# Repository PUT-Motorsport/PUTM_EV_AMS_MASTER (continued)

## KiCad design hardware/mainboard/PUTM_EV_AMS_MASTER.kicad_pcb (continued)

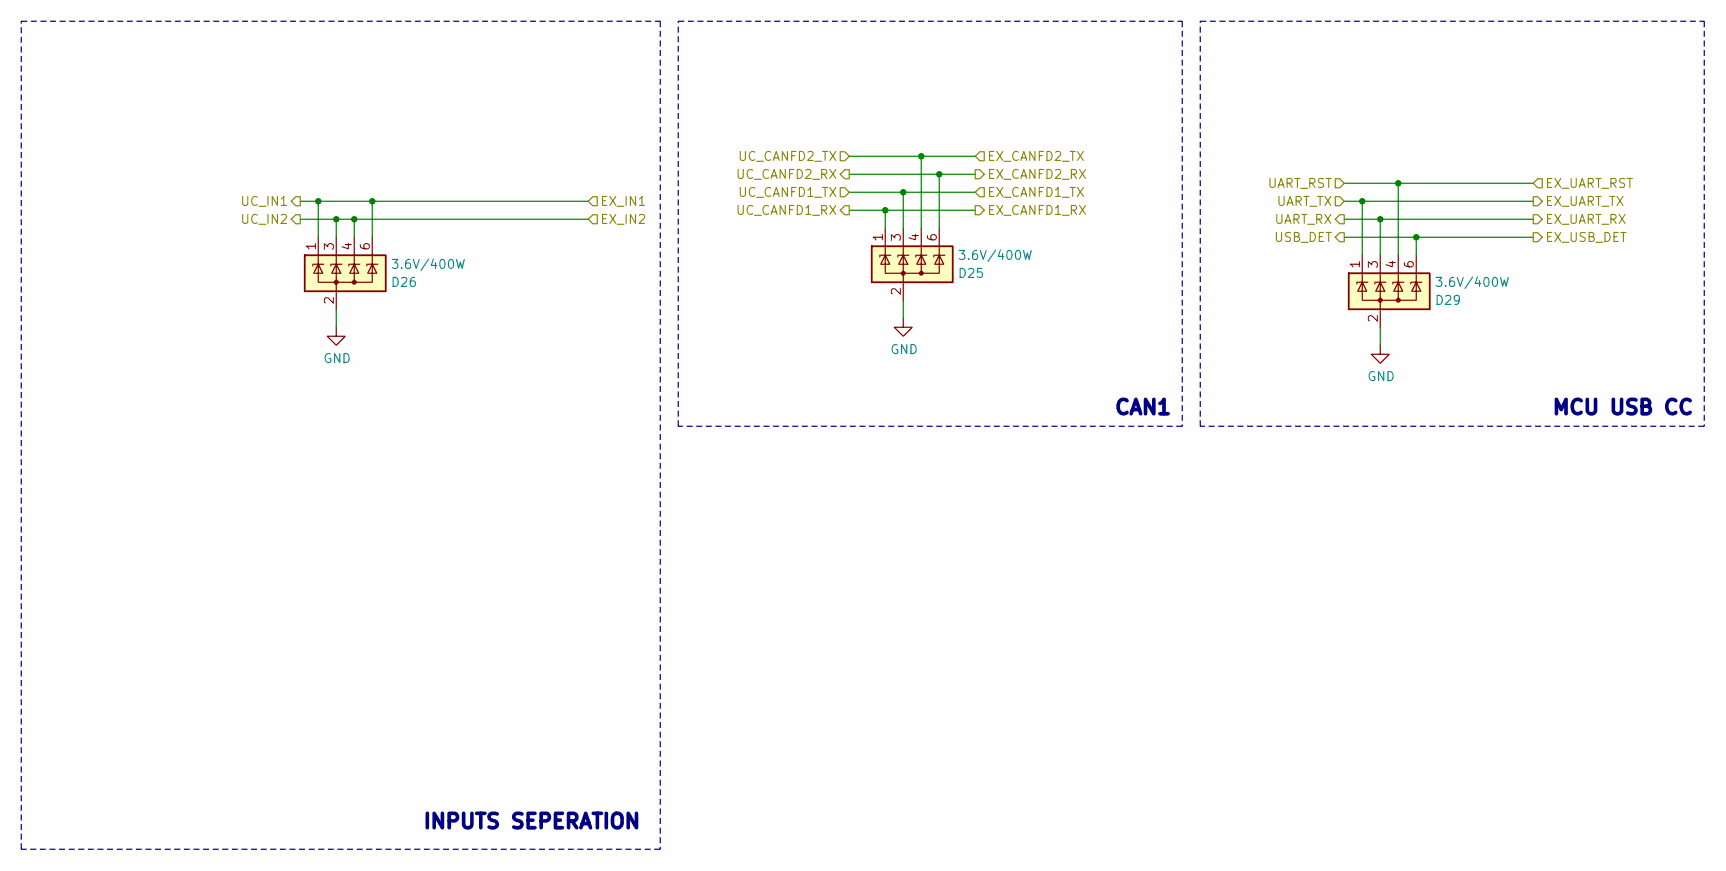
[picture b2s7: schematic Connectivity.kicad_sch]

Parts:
D25, D26, D29: 3.6V/400W; SOT-23-6; Manufacturer_Part_Number ESDS304DBVR; Mouser Part Number 595-ESDS304DBVR

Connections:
/CHARGER_DETECTION: D26.3 (A), D26.4 (A); also elsewhere on the board
/DET_USB: D29.6 (A); also elsewhere on the board
/EX_CANFD1_RX: D25.1 (A); also elsewhere on the board
/EX_CANFD1_TX: D25.3 (A); also elsewhere on the board
/EX_CANFD2_RX: D25.6 (A); also elsewhere on the board
/EX_CANFD2_TX: D25.4 (A); also elsewhere on the board
/TSMS_DETECTION: D26.1 (A), D26.6 (A); also elsewhere on the board
/UART_RST: D29.4 (A); also elsewhere on the board
/UART_RX: D29.3 (A); also elsewhere on the board
/UART_TX: D29.1 (A); also elsewhere on the board
GND: D25.2 (K), D25.5 (NC), D26.2 (K), D26.5 (NC), D29.2 (K), D29.5 (NC); also elsewhere on the board

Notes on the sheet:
CAN1
INPUTS SEPERATION
MCU USB CC

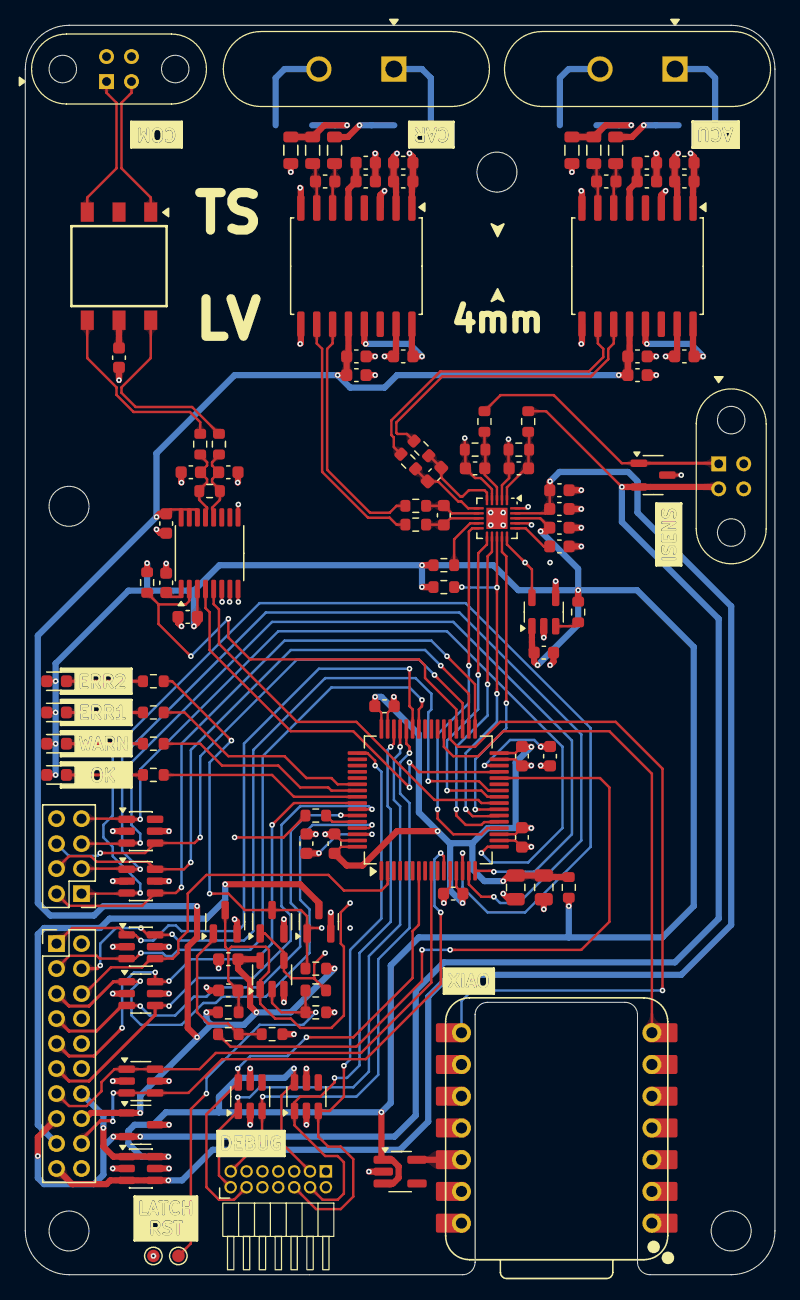
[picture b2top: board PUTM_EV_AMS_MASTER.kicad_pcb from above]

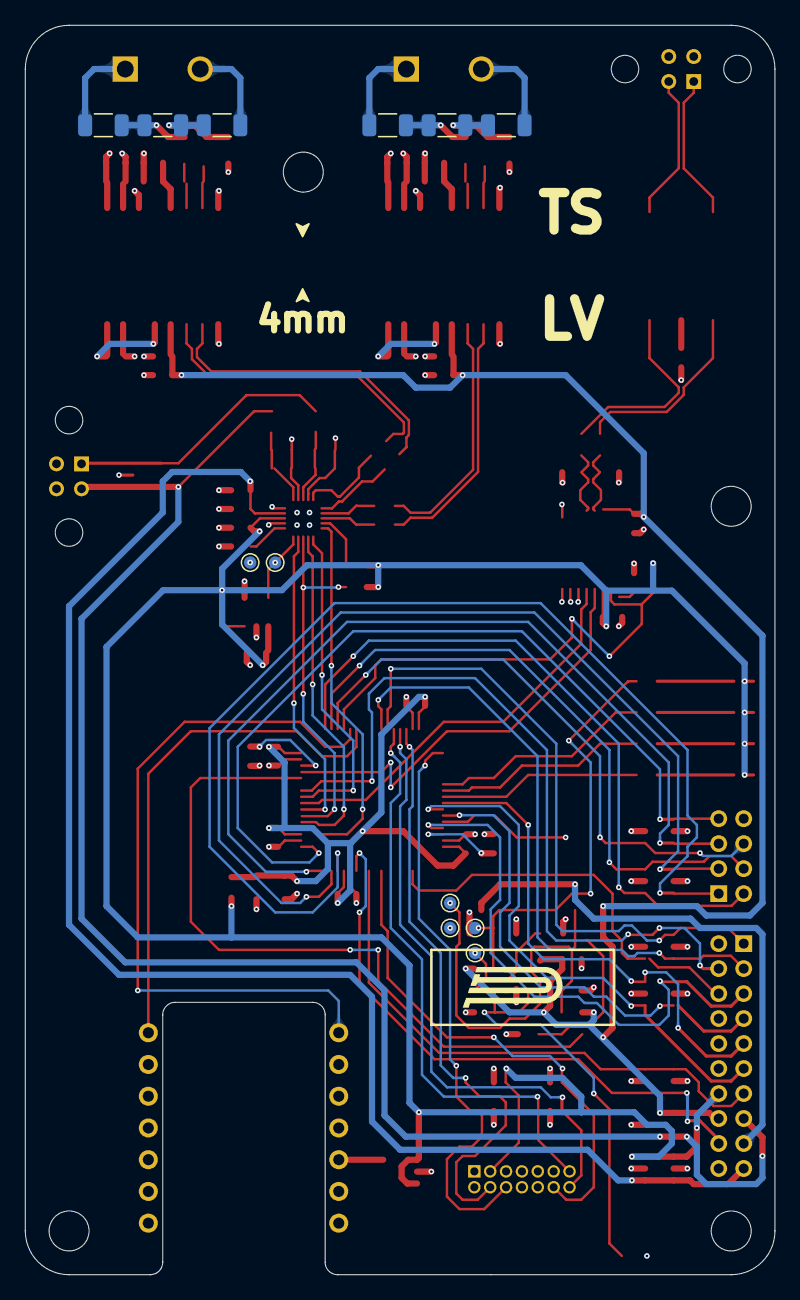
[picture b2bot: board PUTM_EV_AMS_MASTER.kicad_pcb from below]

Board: 4 copper layers, 60.0 x 100.0 mm, 127 parts (12 on the bottom side), 99 nets.

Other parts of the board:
H1, H2, H3, H3#2: M3; MountingHole_3.2mm_M3

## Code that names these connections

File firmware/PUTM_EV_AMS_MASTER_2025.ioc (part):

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Mcu.Name=STM32H573RITx
Mcu.Package=LQFP64
Mcu.UserName=STM32H573RITx
PA0.GPIOParameters=GPIO_Label
PA0.GPIO_Label=FAN1_CTRL
PA0.Signal=S_TIM2_CH1
PA1.GPIOParameters=GPIO_Label
PA1.GPIO_Label=FAN2_CTRL
PA1.Signal=S_TIM2_CH2
PA10.GPIOParameters=GPIO_Label
PA10.GPIO_Label=UART_USB_RX
PA10.Mode=Asynchronous
PA10.Signal=USART1_RX
PA11.GPIOParameters=GPIO_Label
PA11.GPIO_Label=UART_DEBUG_RX
PA11.Mode=Asynchronous
PA11.Signal=UART4_RX
PA12.GPIOParameters=GPIO_Label
PA12.GPIO_Label=UART_DEBUG_TX
PA12.Mode=Asynchronous
PA12.Signal=UART4_TX
PA13(JTMS/SWDIO).Mode=Serial_Wire
PA13(JTMS/SWDIO).Signal=DEBUG_JTMS-SWDIO
PA14(JTCK/SWCLK).Mode=Serial_Wire
PA14(JTCK/SWCLK).Signal=DEBUG_JTCK-SWCLK
PA2.GPIOParameters=GPIO_Label
PA2.GPIO_Label=FAN3_CTRL
PA2.Signal=S_TIM2_CH3
PA3.GPIOParameters=GPIO_Label
PA3.GPIO_Label=FAN4_CTRL
PA3.Signal=S_TIM2_CH4
PA4.GPIOParameters=GPIO_Label
PA4.GPIO_Label=ADC_NSS
PA4.Mode=NSS_Signal_Hard_Output
PA4.Signal=SPI1_NSS
PA5.GPIOParameters=GPIO_Label
PA5.GPIO_Label=ADC_SCK
PA5.Mode=Full_Duplex_Master
PA5.Signal=SPI1_SCK
PA6.GPIOParameters=GPIO_Label
PA6.GPIO_Label=ADC_MISO
PA6.Mode=Full_Duplex_Master
PA6.Signal=SPI1_MISO
PA7.GPIOParameters=GPIO_Label
PA7.GPIO_Label=ADC_MOSI
PA7.Mode=Full_Duplex_Master
PA7.Signal=SPI1_MOSI
PA9.GPIOParameters=GPIO_Label
PA9.GPIO_Label=UART_USB_TX
PA9.Mode=Asynchronous
PA9.Signal=USART1_TX
PB0.Signal=ADCx_INP9
PB10.GPIOParameters=GPIO_Label
PB10.GPIO_Label=UART_COM_TX
PB10.Mode=Asynchronous
PB10.Signal=USART3_TX
PB12.GPIOParameters=GPIO_Label
PB12.GPIO_Label=SIG_AIR_PRE
PB12.Signal=GPIO_Output
PB13.GPIOParameters=GPIO_Label
PB13.GPIO_Label=SIG_AIR_P
PB13.Signal=GPIO_Output
PB14.GPIOParameters=GPIO_Label
PB14.GPIO_Label=SIG_AIR_M
PB14.Signal=GPIO_Output
PB15.GPIOParameters=GPIO_Label
PB15.GPIO_Label=NFLT
PB15.Signal=GPIO_Input
PB2.GPIOParameters=GPIO_Label
PB2.GPIO_Label=SIG_AMS_ERROR
PB2.Signal=GPIO_Output
PB3(JTDO/TRACESWO).GPIOParameters=GPIO_Label
PB3(JTDO/TRACESWO).GPIO_Label=LED_WARNING
PB3(JTDO/TRACESWO).Signal=GPIO_Output
PB4(NJTRST).GPIOParameters=GPIO_Label
PB4(NJTRST).GPIO_Label=LED_OK
PB4(NJTRST).Signal=GPIO_Output
PB5.GPIOParameters=GPIO_Speed
PB5.GPIO_Speed=GPIO_SPEED_FREQ_LOW
PB5.Mode=FDCAN_Activate
PB5.Signal=FDCAN2_RX
PB6.GPIOParameters=GPIO_Speed
PB6.GPIO_Speed=GPIO_SPEED_FREQ_LOW
PB6.Mode=FDCAN_Activate
PB6.Signal=FDCAN2_TX
PB7.Mode=FDCAN_Activate
PB7.Signal=FDCAN1_TX
PB8.Mode=FDCAN_Activate
PB8.Signal=FDCAN1_RX
PC0.GPIOParameters=GPIO_PuPd,GPIO_Label
PC0.GPIO_Label=DET_AIR_PRE
PC0.GPIO_PuPd=GPIO_PULLUP
PC0.Signal=GPIO_Input
PC1.GPIOParameters=GPIO_PuPd,GPIO_Label
PC1.GPIO_Label=DET_TSMS
PC1.GPIO_PuPd=GPIO_PULLUP
PC1.Signal=GPIO_Input
PC13.GPIOParameters=GPIO_Label
PC13.GPIO_Label=USB_RESET
PC13.Signal=GPIO_Output
PC15-OSC32_OUT(OSC32_OUT).GPIOParameters=GPIO_PuPd,GPIO_Label
PC15-OSC32_OUT(OSC32_OUT).GPIO_Label=DET_AIR_P
PC15-OSC32_OUT(OSC32_OUT).GPIO_PuPd=GPIO_PULLUP
PC15-OSC32_OUT(OSC32_OUT).Signal=GPIO_Input
PC2.GPIOParameters=GPIO_PuPd,GPIO_Label
PC2.GPIO_Label=DET_AIR_M
PC2.GPIO_PuPd=GPIO_PULLUP
PC2.Signal=GPIO_Input
PC3.GPIOParameters=GPIO_PuPd,GPIO_Label
PC3.GPIO_Label=DET_CHARGER
PC3.GPIO_PuPd=GPIO_PULLUP
PC3.Signal=GPIO_Input
PC4.GPIOParameters=GPIO_Label
PC4.GPIO_Label=UART_COM_RX
PC4.Mode=Asynchronous
PC4.Signal=USART3_RX
PC5.GPIOParameters=GPIO_Label
PC5.GPIO_Label=NADC_DRY
PC5.Signal=GPXTI5
PC6.Mode=Asynchronous
PC6.Signal=USART6_TX
PC7.Mode=Asynchronous
PC7.Signal=USART6_RX
PD2.GPIOParameters=GPIO_Label
PD2.GPIO_Label=LED_ERROR
PD2.Signal=GPIO_Output
RCC.HSE_VALUE=50000000
RCC.SYSCLKFreq_VALUE=248000000
RCC.SYSCLKSource=RCC_SYSCLKSOURCE_PLLCLK
board=custom

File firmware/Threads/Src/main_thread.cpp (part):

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using namespace Utils;

/* Wrappers */
Gpio led_err(LED_ERROR_GPIO_Port, LED_ERROR_Pin, true);
Gpio led_wrn(LED_WARNING_GPIO_Port, LED_WARNING_Pin, true);
Gpio led_ok(LED_OK_GPIO_Port, LED_OK_Pin, true);
Gpio sig_err(SIG_AMS_ERROR_GPIO_Port, SIG_AMS_ERROR_Pin, true);
Gpio sig_air_pre(SIG_AIR_PRE_GPIO_Port, SIG_AIR_PRE_Pin, false);
Gpio sig_air_p(SIG_AIR_P_GPIO_Port, SIG_AIR_P_Pin, false);
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Gpio det_tsms(DET_TSMS_GPIO_Port, DET_TSMS_Pin, true);
Gpio det_charger(DET_CHARGER_GPIO_Port, DET_CHARGER_Pin, true);
Gpio usb_reset(USB_RESET_GPIO_Port, USB_RESET_Pin, true);
// Gpio adc_dry(ADC_NDRY_GPIO_Port, ADC_NDRY_Pin, true);
// Gpio bq_flt(NFLT_GPIO_Port, NFLT_Pin, true);

constexpr Polynomial t_r_poly { CONFIG::POLYNOMIAL_T_R::COEFFS<NTCPart::DEFAULT> }; //CONFIG::POLYNOMIAL_T_R::COEFFS<NTCType::_10k_3434K>
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 *
 * In the main loop, the following operations are performed periodically:
 * - Toggles the "OK" LED to indicate the thread is alive.
 * - Reads GPIO inputs for TSMS and charger detection.
 * - Updates the SoC for each cell based on voltage, current, and charger status.
 * - Calculates the average SoC across all cells.
 * - Updates cell temperatures using voltage readings and a polynomial evaluation.
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
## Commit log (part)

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2025-02-18 more war with the c++
2025-02-19 code experiments
2025-02-19 sync
2025-02-20 adc communication established, some data is aquired, needs further testing
2025-02-21 syn ti ic reg lib in progress
2025-02-21 firmware sync
2025-02-23 some bq shit
2025-02-23 added a script which modifies hal spi libs - project builds
2025-02-28 new branch for cmake software
2025-02-28 cmake project
2025-02-28 erased tmp folder
2025-03-01 build folder erase
2025-03-01 .gitignore added ignore build folder
2025-03-04 sync???
2025-03-09 save changes
2025-03-09 changing bq79600 com from spi to uart in progress
2025-03-10 changed from spi to uart for bq79600 comm will need to change to code to
2025-03-11 change for bq to uart is done? time to test, but first need to end the read fn
2025-03-11 uart version testing in progress
2025-03-12 not working, implemented send works (verified), but issues with read?????? idk man
2025-03-21 soft sync
2025-03-22 changed logic of bq lib from non blocking to await
2025-03-23 gimodules update, new dir strucure
2025-03-23 .gitmodue test2
2025-03-23 test part 3
2025-03-23 submodule fix and new folder location
2025-03-23 canfd config
2025-03-23 fdcan2 works fdcan1 doesnt (rx and tx is crossed)
2025-03-25 gitmodule update
2025-03-25 git modules fix
2025-03-29 not working usb version
2025-03-29 st usb device removed
2025-03-29 kicad auto save & lck remove
2025-04-01 migration to threadx + usbx, tested ads131m04, bq796xx yet to be tested, new project structure, itd
2025-04-01 Added Arduino json
2025-04-04 threadx done, usbx kinda (not) working
2025-04-05 state machine
2025-04-11 errors work
2025-04-12 error codes in progress
2025-04-13 errors in work
2025-04-15 errors
2025-04-17 errors done? still in testing adding bq temps
2025-04-20 test mode implementation in progress
2025-04-26 ebebebeb
2025-04-27 tests
2025-05-23 hard v3.2.0 init + folder restructure if a second board will be needed
2025-05-26 schematic?
2025-05-27 layout
2025-05-27 one stack (2 devs) less
2025-06-09 hardware routing done, only touch ups will be needed if the board is aproved
2025-06-18 v3.3
2025-06-22 ebebebe
2025-07-11 working new bq lib and uart wrapper
2025-07-12 linux changes
2025-07-13 mx changes, new pinout
2025-07-20 still needs a few tweeks, there was sth wrong with the temp measurement gotta check that
2025-07-23 new temp poly
2025-08-12 working ver i guess?
2025-08-16 gimela fest
2025-08-31 isolation with every thing
2025-09-05 isolated side, choose most components, some master changes tbc
2025-09-27 fix: added go to shutdown command for Bbq79616, in hopes that they will go to shutdown and draw only ~28uA
2025-09-29 chore: sync
2025-09-30 chore:sync
2026-03-19 jenrzej colab
2026-03-21 Cleaned up schematic, changed USB to UART, changed pinout of AIR sandwich connector
2026-03-21 Routed AIR detection signal to main connector
2026-03-21 First board revision
2026-03-21 Fixed silkscreen oopsie
2026-03-22 Layout ver.2
2026-03-23 New HV layout and also a lazy prolly bad main layout that i didnt think much about yet tbh
2026-03-24 Layout again
2026-03-24 minifix
2026-03-24 minifix2
2026-03-24 Plytka chyba fajnie zrobiona oprocz teardropow bo kicad 10 jest dziwny
2026-03-25 Fixed MCU Caps
2026-03-25 Better silkscreen placement and routing
2026-03-25 Take a wild guess. (Its routing fixes)
2026-03-25 Poprawa thermal relief
2026-03-25 isolation schematich done
2026-03-27 moved j8 and one mh slighlty for a better fit overall wih isolation part
2026-03-27 Poprawne wykluczenia DRC i lekka poprawa GND plane
2026-03-28 pcb finished
2026-03-28 manufacturing tweaks
2026-03-28 gnd small fix
2026-03-28 production
2026-05-03 relay fix and changed ic PN for isolated rx/tx for usb to a type with standard output low instead of high
2026-05-03 few touchups in track routing
2026-05-03 made bigger gap span between isolated ground planes
2026-05-11 ground planes fix up
2026-06-01 master main board changes in progress
2026-06-27 removved old can lib
2026-06-29 can fix, added tx/rx loop compensation and tweaked the can config
2026-06-29 soc estimation from screen shots xd
